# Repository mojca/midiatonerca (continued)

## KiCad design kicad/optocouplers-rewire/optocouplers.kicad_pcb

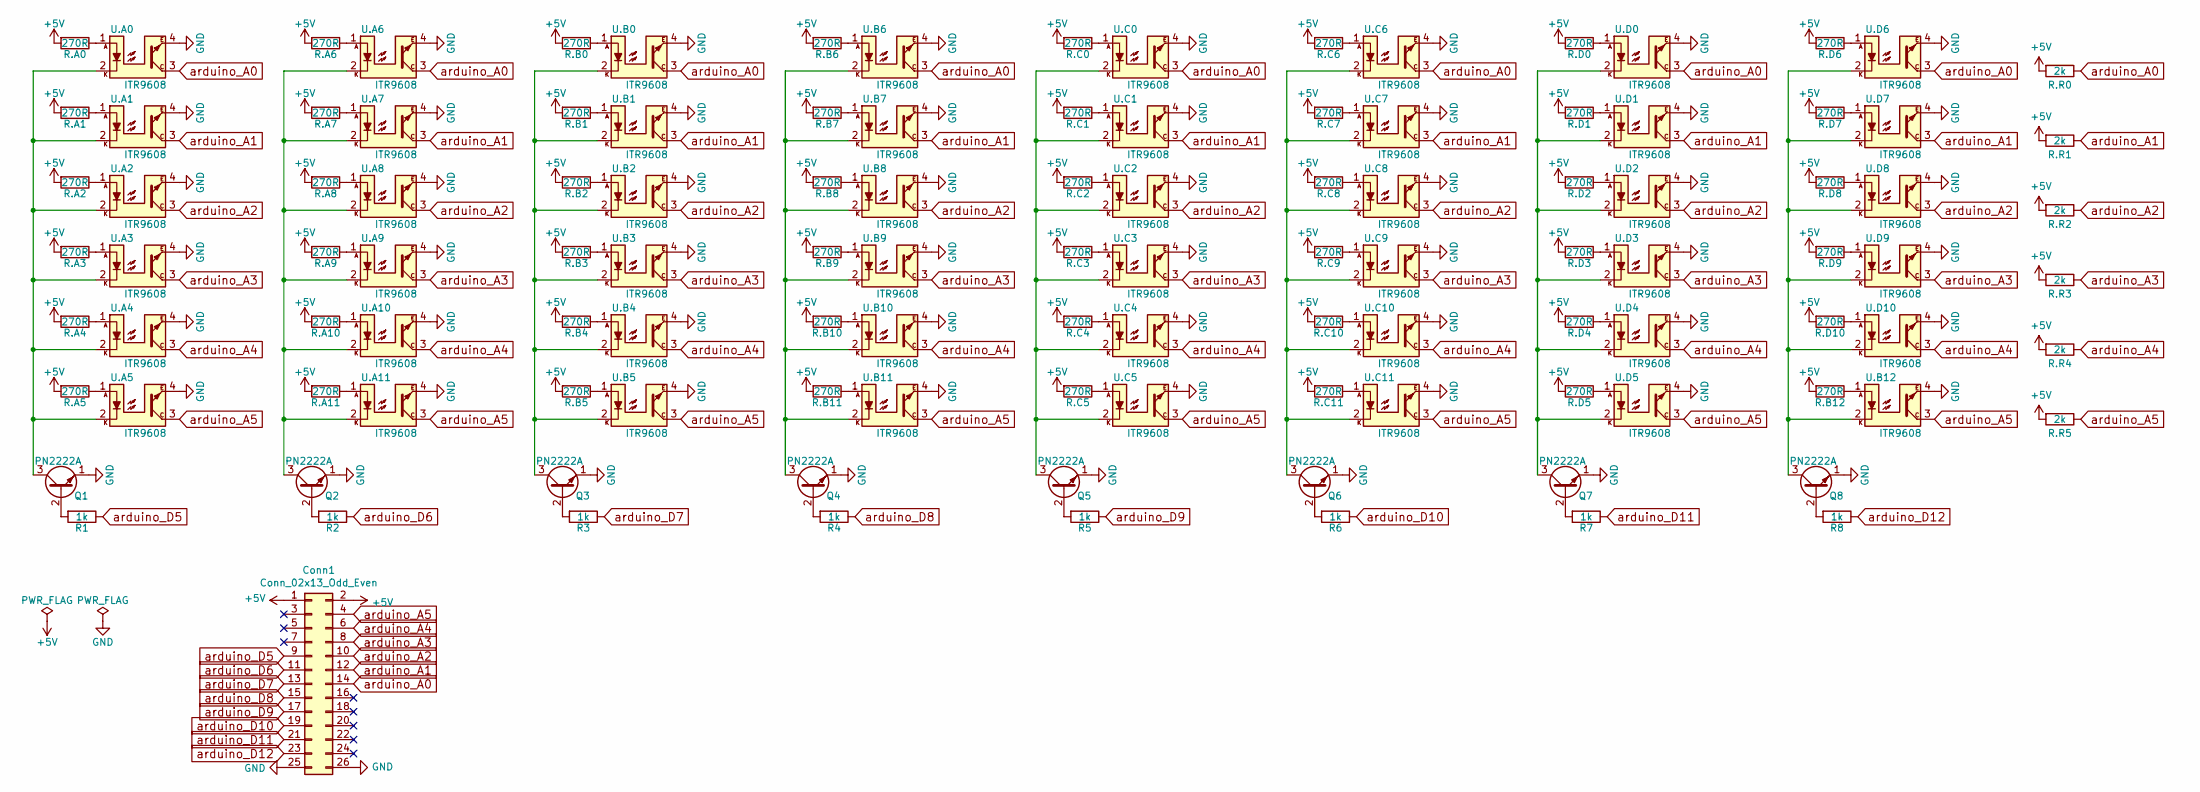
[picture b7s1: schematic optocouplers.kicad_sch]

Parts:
Conn1: Conn_02x13_Odd_Even; IDC-Header_2x13_P2.54mm_Vertical; LCSC Part # C692426
Q1, Q2, Q3, Q4, Q5, Q6, Q7, Q8: PN2222A; TO-92_Inline_Wide; LCSC Part # C184875
R1, R2, R3, R4, R5, R6, R7, R8: 1k; R_1206_3216Metric_Pad1.30x1.75mm_HandSolder; LCSC Part # C4410
R.A0, R.A1, R.A2, R.A3, R.A4, R.A5, R.A6, R.A7, R.A8, R.A9, R.A10, R.A11, R.B0, R.B1, R.B2, R.B3, R.B4, R.B5, R.B6, R.B7, R.B8, R.B9, R.B10, R.B11, R.B12, R.C0, R.C1, R.C2, R.C3, R.C4, R.C5, R.C6, R.C7, R.C8, R.C9, R.C10, R.C11, R.D0, R.D1, R.D2, R.D3, R.D4, R.D5, R.D6, R.D7, R.D8, R.D9, R.D10: 270R; R_1206_3216Metric_Pad1.30x1.75mm_HandSolder; LCSC Part # C229488
R.R0, R.R1, R.R2, R.R3, R.R4, R.R5: 2k; R_1206_3216Metric_Pad1.30x1.75mm_HandSolder; LCSC Part # C17944
U.A0, U.A1, U.A2, U.A3, U.A4, U.A5, U.A6, U.A7, U.A8, U.A9, U.A10, U.A11, U.B0, U.B1, U.B2, U.B3, U.B4, U.B5, U.B6, U.B7, U.B8, U.B9, U.B10, U.B11, U.B12, U.C0, U.C1, U.C2, U.C3, U.C4, U.C5, U.C6, U.C7, U.C8, U.C9, U.C10, U.C11, U.D0, U.D1, U.D2, U.D3, U.D4, U.D5, U.D6, U.D7, U.D8, U.D9, U.D10: ITR9608; LCSC Part # C52833

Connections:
+5V: Conn1.1, Conn1.2, R.A0.2, R.A1.2, R.A2.2, R.A3.2, R.A4.2, R.A5.2, R.A6.2, R.A7.2, R.A8.2, R.A9.2, R.A10.2, R.A11.2, R.B0.2, R.B1.2, R.B2.2, R.B3.2, R.B4.2, R.B5.2, R.B6.2, R.B7.2, R.B8.2, R.B9.2, R.B10.2, R.B11.2, R.B12.2, R.C0.2, R.C1.2, R.C2.2, R.C3.2, R.C4.2, R.C5.2, R.C6.2, R.C7.2, R.C8.2, R.C9.2, R.C10.2, R.C11.2, R.D0.2, R.D1.2, R.D2.2, R.D3.2, R.D4.2, R.D5.2, R.D6.2, R.D7.2, R.D8.2, R.D9.2, R.D10.2, R.R0.2, R.R1.2, R.R2.2, R.R3.2, R.R4.2, R.R5.2
GND: Conn1.25, Conn1.26, Q1.1 (E), Q2.1 (E), Q3.1 (E), Q4.1 (E), Q5.1 (E), Q6.1 (E), Q7.1 (E), Q8.1 (E), U.A0.4, U.A1.4, U.A2.4, U.A3.4, U.A4.4, U.A5.4, U.A6.4, U.A7.4, U.A8.4, U.A9.4, U.A10.4, U.A11.4, U.B0.4, U.B1.4, U.B2.4, U.B3.4, U.B4.4, U.B5.4, U.B6.4, U.B7.4, U.B8.4, U.B9.4, U.B10.4, U.B11.4, U.B12.4, U.C0.4, U.C1.4, U.C2.4, U.C3.4, U.C4.4, U.C5.4, U.C6.4, U.C7.4, U.C8.4, U.C9.4, U.C10.4, U.C11.4, U.D0.4, U.D1.4, U.D2.4, U.D3.4, U.D4.4, U.D5.4, U.D6.4, U.D7.4, U.D8.4, U.D9.4, U.D10.4
unnamed: Q1.2 (B), R1.2
unnamed: Q1.3 (C), U.A0.2, U.A1.2, U.A2.2, U.A3.2, U.A4.2, U.A5.2
unnamed: Q2.2 (B), R2.2
unnamed: Q2.3 (C), U.A6.2, U.A7.2, U.A8.2, U.A9.2, U.A10.2, U.A11.2
unnamed: Q3.2 (B), R3.2
unnamed: Q3.3 (C), U.B0.2, U.B1.2, U.B2.2, U.B3.2, U.B4.2, U.B5.2
unnamed: Q4.2 (B), R4.2
unnamed: Q4.3 (C), U.B6.2, U.B7.2, U.B8.2, U.B9.2, U.B10.2, U.B11.2
unnamed: Q5.2 (B), R5.2
unnamed: Q5.3 (C), U.C0.2, U.C1.2, U.C2.2, U.C3.2, U.C4.2, U.C5.2
unnamed: Q6.2 (B), R6.2
unnamed: Q6.3 (C), U.C6.2, U.C7.2, U.C8.2, U.C9.2, U.C10.2, U.C11.2
unnamed: Q7.2 (B), R7.2
unnamed: Q7.3 (C), U.D0.2, U.D1.2, U.D2.2, U.D3.2, U.D4.2, U.D5.2
unnamed: Q8.2 (B), R8.2
unnamed: Q8.3 (C), U.B12.2, U.D6.2, U.D7.2, U.D8.2, U.D9.2, U.D10.2
unnamed: R.A0.1, U.A0.1
unnamed: R.A1.1, U.A1.1
unnamed: R.A2.1, U.A2.1
unnamed: R.A3.1, U.A3.1
unnamed: R.A4.1, U.A4.1
unnamed: R.A5.1, U.A5.1
unnamed: R.A6.1, U.A6.1
unnamed: R.A7.1, U.A7.1
unnamed: R.A8.1, U.A8.1
unnamed: R.A9.1, U.A9.1
unnamed: R.A10.1, U.A10.1
unnamed: R.A11.1, U.A11.1
unnamed: R.B0.1, U.B0.1
unnamed: R.B1.1, U.B1.1
unnamed: R.B2.1, U.B2.1
unnamed: R.B3.1, U.B3.1
unnamed: R.B4.1, U.B4.1
unnamed: R.B5.1, U.B5.1
unnamed: R.B6.1, U.B6.1
unnamed: R.B7.1, U.B7.1
unnamed: R.B8.1, U.B8.1
unnamed: R.B9.1, U.B9.1
unnamed: R.B10.1, U.B10.1
unnamed: R.B11.1, U.B11.1
unnamed: R.B12.1, U.B12.1
unnamed: R.C0.1, U.C0.1
unnamed: R.C1.1, U.C1.1
unnamed: R.C2.1, U.C2.1
unnamed: R.C3.1, U.C3.1
unnamed: R.C4.1, U.C4.1
unnamed: R.C5.1, U.C5.1
unnamed: R.C6.1, U.C6.1
unnamed: R.C7.1, U.C7.1
unnamed: R.C8.1, U.C8.1
unnamed: R.C9.1, U.C9.1
unnamed: R.C10.1, U.C10.1
unnamed: R.C11.1, U.C11.1
unnamed: R.D0.1, U.D0.1
unnamed: R.D1.1, U.D1.1
unnamed: R.D2.1, U.D2.1
unnamed: R.D3.1, U.D3.1
unnamed: R.D4.1, U.D4.1
unnamed: R.D5.1, U.D5.1
unnamed: R.D6.1, U.D6.1
unnamed: R.D7.1, U.D7.1
unnamed: R.D8.1, U.D8.1
unnamed: R.D9.1, U.D9.1
unnamed: R.D10.1, U.D10.1
arduino_A0: Conn1.14, R.R0.1, U.A0.3, U.A6.3, U.B0.3, U.B6.3, U.C0.3, U.C6.3, U.D0.3, U.D6.3
arduino_A1: Conn1.12, R.R1.1, U.A1.3, U.A7.3, U.B1.3, U.B7.3, U.C1.3, U.C7.3, U.D1.3, U.D7.3
arduino_A2: Conn1.10, R.R2.1, U.A2.3, U.A8.3, U.B2.3, U.B8.3, U.C2.3, U.C8.3, U.D2.3, U.D8.3
arduino_A3: Conn1.8, R.R3.1, U.A3.3, U.A9.3, U.B3.3, U.B9.3, U.C3.3, U.C9.3, U.D3.3, U.D9.3
arduino_A4: Conn1.6, R.R4.1, U.A4.3, U.A10.3, U.B4.3, U.B10.3, U.C4.3, U.C10.3, U.D4.3, U.D10.3
arduino_A5: Conn1.4, R.R5.1, U.A5.3, U.A11.3, U.B5.3, U.B11.3, U.B12.3, U.C5.3, U.C11.3, U.D5.3
arduino_D5: Conn1.9, R1.1
arduino_D6: Conn1.11, R2.1
arduino_D7: Conn1.13, R3.1
arduino_D8: Conn1.15, R4.1
arduino_D9: Conn1.17, R5.1
arduino_D10: Conn1.19, R6.1
arduino_D11: Conn1.21, R7.1
arduino_D12: Conn1.23, R8.1

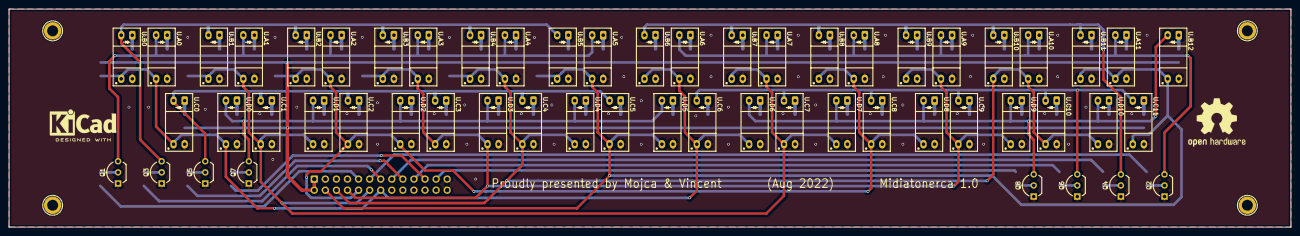
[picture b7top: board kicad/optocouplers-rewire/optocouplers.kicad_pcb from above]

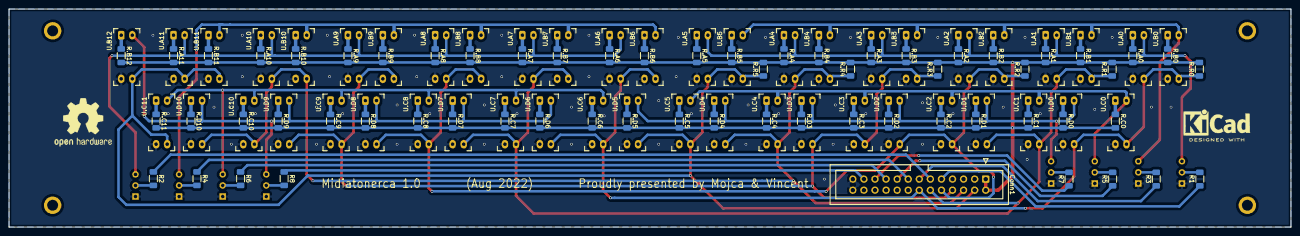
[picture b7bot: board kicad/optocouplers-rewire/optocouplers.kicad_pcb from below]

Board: 2 copper layers, 294.0 x 50.0 mm, 119 parts (63 on the bottom side), 80 nets.

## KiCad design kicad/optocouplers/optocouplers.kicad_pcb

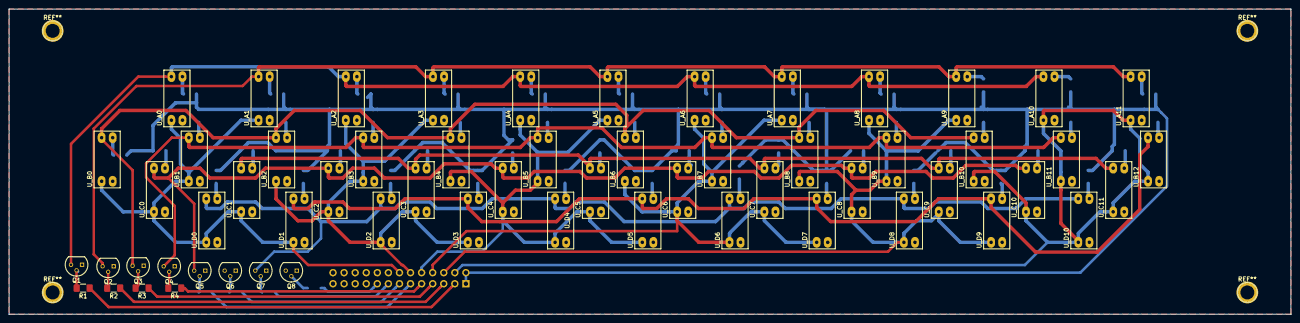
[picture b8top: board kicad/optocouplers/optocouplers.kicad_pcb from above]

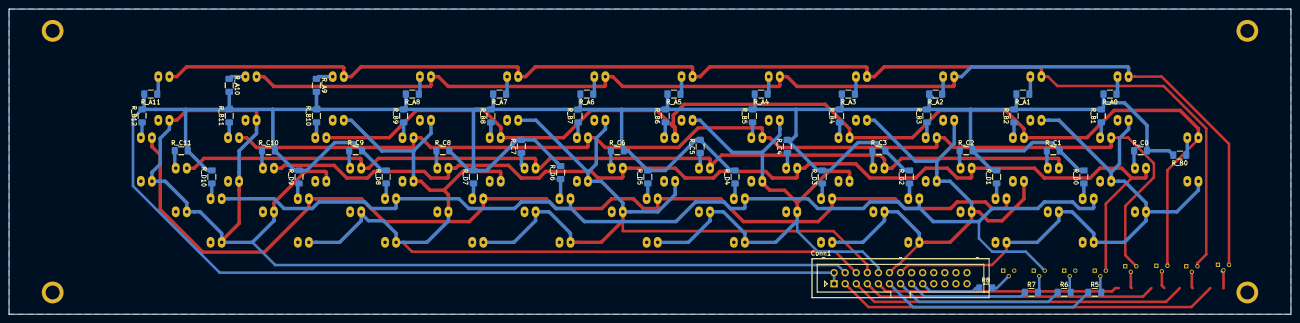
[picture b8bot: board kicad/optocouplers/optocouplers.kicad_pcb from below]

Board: 2 copper layers, 294.0 x 70.0 mm, 113 parts (53 on the bottom side), 80 nets.

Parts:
Conn1: Conn_02x13_Odd_Even; Multicomp_MC9A12-2634_2x13_P2.54mm_Vertical
Q1, Q2, Q3, Q4, Q5, Q6, Q7, Q8: PN2222A; TO-92_Molded_Narrow
R1, R2, R3, R4, R5, R6, R7, R8: 1k; R_1206_3216Metric_Pad1.42x1.75mm_HandSolder
R_A0, R_A1, R_A2, R_A3, R_A4, R_A5, R_A6, R_A7, R_A8, R_A9, R_A10, R_A11: 270R; R_1206_3216Metric_Pad1.42x1.75mm_HandSolder
R_B0, R_B1, R_B2, R_B3, R_B4, R_B5, R_B6, R_B7, R_B8, R_B9, R_B10, R_B11, R_B12: 270R; R_1206_3216Metric_Pad1.42x1.75mm_HandSolder
R_C0, R_C1, R_C2, R_C3, R_C4, R_C5, R_C6, R_C7, R_C8, R_C9, R_C10, R_C11: 270R; R_1206_3216Metric_Pad1.42x1.75mm_HandSolder
R_D0, R_D1, R_D2, R_D3, R_D4, R_D5, R_D6, R_D7, R_D8, R_D9, R_D10: 270R; R_1206_3216Metric_Pad1.42x1.75mm_HandSolder
U_A0, U_A1, U_A2, U_A3, U_A4, U_A5, U_A6, U_A7, U_A8, U_A9, U_A10, U_A11: ITR9608
U_B0, U_B1, U_B2, U_B3, U_B4, U_B5, U_B6, U_B7, U_B8, U_B9, U_B10, U_B11, U_B12: ITR9608
U_C0, U_C1, U_C2, U_C3, U_C4, U_C5, U_C6, U_C7, U_C8, U_C9, U_C10, U_C11: ITR9608
U_D0, U_D1, U_D2, U_D3, U_D4, U_D5, U_D6, U_D7, U_D8, U_D9, U_D10: ITR9608

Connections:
+5V: Conn1.1, Conn1.2, R_A0.2, R_A1.2, R_A2.2, R_A3.2, R_A4.2, R_A5.2, R_A6.2, R_A7.2, R_A8.2, R_A9.2, R_A10.2, R_A11.2, R_B0.2, R_B1.2, R_B2.2, R_B3.2, R_B4.2, R_B5.2, R_B6.2, R_B7.2, R_B8.2, R_B9.2, R_B10.2, R_B11.2, R_B12.2, R_C0.2, R_C1.2, R_C2.2, R_C3.2, R_C4.2, R_C5.2, R_C6.2, R_C7.2, R_C8.2, R_C9.2, R_C10.2, R_C11.2, R_D0.2, R_D1.2, R_D2.2, R_D3.2, R_D4.2, R_D5.2, R_D6.2, R_D7.2, R_D8.2, R_D9.2, R_D10.2
GND: Conn1.25, Conn1.26, Q1.1, Q2.1, Q3.1, Q4.1, Q5.1, Q6.1, Q7.1, Q8.1, U_A0.4, U_A1.4, U_A2.4, U_A3.4, U_A4.4, U_A5.4, U_A6.4, U_A7.4, U_A8.4, U_A9.4, U_A10.4, U_A11.4, U_B0.4, U_B1.4, U_B2.4, U_B3.4, U_B4.4, U_B5.4, U_B6.4, U_B7.4, U_B8.4, U_B9.4, U_B10.4, U_B11.4, U_B12.4, U_C0.4, U_C1.4, U_C2.4, U_C3.4, U_C4.4, U_C5.4, U_C6.4, U_C7.4, U_C8.4, U_C9.4, U_C10.4, U_C11.4, U_D0.4, U_D1.4, U_D2.4, U_D3.4, U_D4.4, U_D5.4, U_D6.4, U_D7.4, U_D8.4, U_D9.4, U_D10.4
unnamed: Q1.2, R1.2
unnamed: Q1.3, U_A0.2, U_A2.2, U_A4.2, U_A6.2, U_A8.2, U_A10.2
unnamed: Q2.2, R2.2
unnamed: Q2.3, U_A1.2, U_A3.2, U_A5.2, U_A7.2, U_A9.2, U_A11.2
unnamed: Q3.2, R3.2
unnamed: Q3.3, U_B0.2, U_B2.2, U_B4.2, U_B6.2, U_B8.2, U_B10.2
unnamed: Q4.2, R4.2
unnamed: Q4.3, U_B1.2, U_B3.2, U_B5.2, U_B7.2, U_B9.2, U_B11.2
unnamed: Q5.2, R5.2
unnamed: Q5.3, U_C0.2, U_C2.2, U_C4.2, U_C6.2, U_C8.2, U_C10.2
unnamed: Q6.2, R6.2
unnamed: Q6.3, U_C1.2, U_C3.2, U_C5.2, U_C7.2, U_C9.2, U_C11.2
unnamed: Q7.2, R7.2
unnamed: Q7.3, U_D0.2, U_D2.2, U_D4.2, U_D6.2, U_D8.2, U_D10.2
unnamed: Q8.2, R8.2
unnamed: Q8.3, U_B12.2, U_D1.2, U_D3.2, U_D5.2, U_D7.2, U_D9.2
unnamed: R_A0.1, U_A0.1
unnamed: R_A1.1, U_A1.1
unnamed: R_A2.1, U_A2.1
unnamed: R_A3.1, U_A3.1
unnamed: R_A4.1, U_A4.1
unnamed: R_A5.1, U_A5.1
unnamed: R_A6.1, U_A6.1
unnamed: R_A7.1, U_A7.1
unnamed: R_A8.1, U_A8.1
unnamed: R_A9.1, U_A9.1
unnamed: R_A10.1, U_A10.1
unnamed: R_A11.1, U_A11.1
unnamed: R_B0.1, U_B0.1
unnamed: R_B1.1, U_B1.1
unnamed: R_B2.1, U_B2.1
unnamed: R_B3.1, U_B3.1
unnamed: R_B4.1, U_B4.1
unnamed: R_B5.1, U_B5.1
unnamed: R_B6.1, U_B6.1
unnamed: R_B7.1, U_B7.1
unnamed: R_B8.1, U_B8.1
unnamed: R_B9.1, U_B9.1
unnamed: R_B10.1, U_B10.1
unnamed: R_B11.1, U_B11.1
unnamed: R_B12.1, U_B12.1
unnamed: R_C0.1, U_C0.1
unnamed: R_C1.1, U_C1.1
unnamed: R_C2.1, U_C2.1
unnamed: R_C3.1, U_C3.1
unnamed: R_C4.1, U_C4.1
unnamed: R_C5.1, U_C5.1
unnamed: R_C6.1, U_C6.1
unnamed: R_C7.1, U_C7.1
unnamed: R_C8.1, U_C8.1
unnamed: R_C9.1, U_C9.1
unnamed: R_C10.1, U_C10.1
unnamed: R_C11.1, U_C11.1
unnamed: R_D0.1, U_D0.1
unnamed: R_D1.1, U_D1.1
unnamed: R_D2.1, U_D2.1
unnamed: R_D3.1, U_D3.1
unnamed: R_D4.1, U_D4.1
unnamed: R_D5.1, U_D5.1
unnamed: R_D6.1, U_D6.1
unnamed: R_D7.1, U_D7.1
unnamed: R_D8.1, U_D8.1
unnamed: R_D9.1, U_D9.1
unnamed: R_D10.1, U_D10.1
arduino_A0: Conn1.14, U_A0.3, U_A1.3, U_B0.3, U_B1.3, U_C0.3, U_C1.3, U_D0.3, U_D1.3
arduino_A1: Conn1.12, U_A2.3, U_A3.3, U_B2.3, U_B3.3, U_C2.3, U_C3.3, U_D2.3, U_D3.3
arduino_A2: Conn1.10, U_A4.3, U_A5.3, U_B4.3, U_B5.3, U_C4.3, U_C5.3, U_D4.3, U_D5.3
arduino_A3: Conn1.8, U_A6.3, U_A7.3, U_B6.3, U_B7.3, U_C6.3, U_C7.3, U_D6.3, U_D7.3
arduino_A4: Conn1.6, U_A8.3, U_A9.3, U_B8.3, U_B9.3, U_C8.3, U_C9.3, U_D8.3, U_D9.3
arduino_A5: Conn1.4, U_A10.3, U_A11.3, U_B10.3, U_B11.3, U_B12.3, U_C10.3, U_C11.3, U_D10.3
arduino_D5: Conn1.3, R1.1
arduino_D6: Conn1.5, R2.1
arduino_D7: Conn1.7, R3.1
arduino_D8: Conn1.9, R4.1
arduino_D9: Conn1.11, R5.1
arduino_D10: Conn1.13, R6.1
arduino_D11: Conn1.15, R7.1
arduino_D12: Conn1.17, R8.1

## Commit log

2017-07-24 revision 3 and 4 of 3D design
2017-07-24 alternative keyboard plates
2017-07-24 dxf files for keyboards
2017-07-26 Version 5 of mechanical design
2017-07-26 test dxf conversion from pstoedit
2017-07-26 test eps
2017-07-26 test dxf
2017-07-26 add dxf files for revision 5
2017-07-26 add zips
2017-07-26 revision 6
2017-07-27 alt keyboard
2017-07-28 optocoupler board
2017-07-31 testing design for the keyboard
2017-07-31 Added schematic for octocoupler backplate
2017-07-31 start creating a pattern
2017-07-31 keyboard pcb: two lines
2017-07-31 full board for keyboard
2017-08-01 nearly final version of keyboard PCB
2017-08-02 Arduino code for LeverHarmonica added
2017-08-03 Single button MIDI latency tester
2017-08-04 Added support for different patches. Serial baudrate now defaults to 31250.
2017-08-04 Add two semitones for the fourth row
2017-08-04 version of printed pcb
2017-08-05 Add handling for the second harmonika
2017-08-05 Fix debounce on second accordion
2019-09-15 Added Arduino project: BassButtonTester. Actually also for testing treble buttons. Different pin assignments can be configured. Analog sensor readings can be inspected, as well as single row/column d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
    BassButton is a class which makes it easy to embed it in different projects and hide the complexity of the implementation.
2022-06-21 Updates bass side etc in Enschede
2022-07-28 SpecialInstrument implemented
2022-07-28 Remove trailing spaces
2022-07-28 Specify buttons with names
2022-07-28 Add an optional test routine which is run if a flag is set
    The test routine continuously produces one simple note.
    Baudrate changed to 115200, to avoid the 31250/38400 bug in SamplerBox.
    Some more corrections and changes and updates.
2022-07-29 Defined bass and chords for 2-row harmonica
2022-07-29 Clean-up bass names
2022-07-29 Fix bass heights
2022-07-29 Added support to count the number of buttons playing the same note.
    Multiple buttons may play the same note. noteON is sent for each one, but noteOFF only for the last one.
2022-07-29 Support for multiple keypresses for the same note.
2022-07-29 Changing patch or instrument now stops notes. Note numbers 0 no longer transferred. Code cleaned up.
    When changing patch or instrument type (2-row or 4-row) the currently playing notes are now stopped, to avoid noteOFF mismatch.
    If note number is 0 then it is no longer sent as noteON or noteOFF to the SamplerBox.
    Code has been cleaned up.
2022-08-01 Add some basic LED lighting and push/pull button
2022-08-01 set serial speed
2022-08-02 Patch updated with new studio recording, and non-midi text messages update
    Patch 0 now contains the studio recording from Aug 1, 2022. The recording in Mojca's room has been moved to patch 15.
    The MIDI message function now only outputs messages if midi note is nonzero, both in midi and non-midi mode.
2022-09-14 New pin and bank mapping, separate include files for midi notes and instrument patches, autodetect switch inversion.
    In the Aug/Sept 2022 update new PCBs were developed for lever and cherry key accordions. The key mapping has changed: instead of 6 banks we now have 8 banks.
    A new project was created: "LeverHarmonica_EightBanks_Sept2022" so that the old project (LeverHarmonica) is still compatible with our 1st iteration (wooden harmonica). In the new project separate hea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
2022-11-23 Added EightBanks version of arduino code
2023-12-28 Implemented Native MIDI in LeverHarmonica_EightBanks script
    Native MIDI is now supported. Nano 33 IoT must be used as Arduino controller from now on. The older Nano 3.0 does not support native MIDI.
    The script is still backwards compatible with Patchbox-style MIDI-over-Serial-over-USB by setting NATIVE_MIDI = false.
2024-01-01 Moved unused versions to subdirectories
2024-01-01 Implemented LEDs
    LEDs willl light up according to:
    depressed, decayTimeMs > decayMax: 10%
    depressed, decayTimeMs < decayMax: map(decayTimeMs, 0, 50, decayMax, 25)
    pressed: 100% (set decayTimeMs = 0)
    released: initially 50%, decays to 25% during one second
2024-01-02 Set MIDI note offsets to 0 for all patches
2024-01-28 Expanded some debugging code to help solving some issues
    Fix stuff
2024-03-04 schematic for optocouplers
2024-03-04 cherry-mx basses
2024-03-04 update kicad drawings for optocouplers
2024-03-04 Add labels to optocoupler board
2024-03-04 Slightly change wiring of optocouplers
2024-03-04 add arduino to cherry keys
2024-03-04 Update to the latest version of optocoupler pcb design
2024-03-04 fix reference names on PCB
2024-03-04 Copy of optocouplers (temporary)
2024-03-04 Add schematic for new optocouplers board
2024-03-04 Assign correct footprint of transistors, missing resistors
2024-03-04 intermediate step of optocoupler pcb
2024-03-04 [PCB] cherry basses: changes in lib
    Not exactly sure what these changes are ...
2024-03-04 Add schematic for cherry treble
2024-03-04 Pick compatible PCB components for cherry trebble
2024-03-04 temp commit with pcb
2024-03-04 Add two mounting holes and refill background of cherry basses
2024-03-04 Add missing 2k resistors, change connectors (opto)
2024-03-04 Backup of optocouplers
2024-03-04 Save cherry basses with kicad 6
2024-03-04 remove all segments from optocouplers board
2024-03-04 Use correct components (.net) for optocouple board
2024-03-04 almost complete pcb
2024-03-04 Almost finished pcb
2024-03-04 This change removed background fill from optocouplers board
    It was probably done by accident and might need reverting
2024-03-04 Fix silkscreen text on cherry basses
2024-03-04 cache lib for optocouplers PCB
2024-03-04 Add edge cut to cherry basses
2024-03-04 unfinished changes in optocouplers board
2024-03-04 Finish cherry basses keyboard
2024-03-04 rename some components in schematic
2024-03-04 Update components
2024-03-04 No clue what this changed (TODO)
2024-03-04 move a single optocoupler
2024-03-04 No clue what changed
2024-03-04 swap a1 and a6
2024-03-04 slightly align two resistors, update pcb from schematic, prepare before fixing names of components
2024-03-04 Remove the background drawing of optocouplers
2024-03-04 Move around optocouplers for rows A and C
2024-03-04 Rename elements on pcb
2024-03-04 remove segments
2024-03-04 Temporary move some resistors around
2024-03-04 Remove the drawing of a single optocoupler
2024-03-04 align optocouplers for line C
2024-03-04 Can the net list be deleted?
2024-03-04 Fix placements of components for the row A
2024-03-04 Fix placement of row b
2024-03-04 change uuids of resistors
2024-03-04 fix placement of components for row D
2024-03-04 rename uuids
2024-03-04 old sch file is no longer needed (optocouplers)
2024-03-04 fix placements of resistors for row c
2024-03-04 move resistors to the back of the list as they belong to the back cu
2024-03-04 Remove paths
2024-03-04 some nearly straight lines
2024-03-04 Place resistors R.R0 to R.R5
2024-03-04 Move optocouplers 1 mm higher (TODO: one resistor belongs to a different commit)
2024-03-04 Move some resistors a bit
2024-03-04 fix resistor location
2024-03-04 straight lines
2024-03-04 fix typo in resistor uuid
2024-03-04 Simple connections between neighbours
2024-03-04 Unfinished PCB for cherry treble
2024-03-04 Exclude cherry switches from BOM
2024-03-04 5V line
2024-03-04 Update wiring schematic for cherry treble
2024-03-04 Some project settings for cherry basses
2024-03-04 Add some lines
2024-03-04 More lines
2024-03-04 Add Neltron connectors
2024-03-04 Update pcb for cherry basses
    - add connector for the side button
    - fix vias
    - fix positions of some diodes
2024-03-04 Update cherry treble PCB
2024-03-04 cherry basses pcb: no clue what changed
2024-03-04 Move connector closer to the keys on cherry treble
    Almost enforce the clearance
2024-03-04 Project and settings for cherry basses
2024-03-04 optocouplers project
2024-03-04 Replace the cherry basses schematic with the new one
2024-03-04 Move optocouplers to the correct place, shrink the board
2024-03-04 optocouplers schematic
2024-03-04 optocouplers prl
2024-03-04 Move pushpull switch name on cherry basses
2024-03-04 Potentially finished cherry treble pcb
2024-03-04 cherry basses: replace components for rendering, add some vias
2024-03-04 Shrink kicad treble, fix interline spacing
2024-03-04 Move elements of the cherry treble PCB
2024-03-04 shrink cherry treble pcb by 2 mm on each side
2024-03-04 Further dimension adjustments to cherry treble to fit into the box
2024-03-04 Define clearance to 0.5 mm for cherry treble
2024-03-04 Refill zones
2024-03-04 Exclude connector on cherry treble from BOM
2024-03-04 Define origin
2024-03-04 optocouplers: change footprints
2024-03-04 Name the diodes on cherry treble
2024-03-04 Exclude connector from position file
2024-03-04 Remove cherry switches from assembly files
2024-03-04 Add part numbers for resistors in cherry treble schematics
2024-03-04 Add LCSC part # for resistors
2024-03-04 Add exclude_from_bom to cherry treble
2024-03-04 Exclude mounting holes from assembly
2024-03-04 Rename diodes on the PCB (probably not needed, might be reverted)
2024-03-04 No clue what this changes in cherry treble prl
2024-03-04 Update optocouplers project
2024-03-04 Refill optocouplers pcb
2024-03-04 gerber settings for optocouplers
2024-03-04 Move the whole optocouplers board a bit up, finish tracing
2024-03-04 Add LCSC part numbers for the optocoupler schematics
2024-03-04 optocouplers, continue wiring
2024-03-04 Add part numbers to optocouplers
2024-03-04 Autoplace fields on cherry treble schematics
2024-03-04 Add kicad & osh symbols to cherry treble pcb
2024-03-04 Use the new footprint for ITR9608
2024-03-04 Replace rescued elements with proper / newer ones
2024-03-04 Blue cherry treble board
2024-03-04 Add text to the optocouplers pcb
2024-03-04 Add arduino port labels
2024-03-04 Update footprints for optocouplers in the PCB
2024-03-04 Avoid 90 degree corners in cherry treble pcb
2024-03-04 Update diodes from schematic and fix polarity on cherry treble pcb
2024-03-04 Update part numbers for the schottky diodes plus whatever refill took place
2024-03-04 Make pcb blue
2024-03-04 Replace diode symbols on cherry treble
2024-03-04 Add OSH and KiCad logos on the silkscreen
2024-03-04 Fix part number for the schottky diodes
2024-03-04 Move led-strip schematic a bit
2024-03-04 Replace pspice diodes with proper schottky diodes on cherry basses schematics
2024-03-04 First arduino plate PCB
2024-03-04 LED strip schematic & pcb
2024-03-04 Add labels to the connector
2024-03-04 Replace mounting holes and update components from library (cherry basses)
2024-03-04 led strip project update
2024-03-04 led strip levers: unfinished PCB
2024-03-04 Add footprint for a mini toggle SPDT switch B068BW
2024-03-04 Add osh logo
2024-03-04 Updates to arduino
2024-03-04 cherry basses: update color, fix diode orientation, remove border from silk screen
2024-03-04 First version of RPi audio hat
2024-03-04 Some rounding changes to the cherry basses pcb
2024-03-04 led strip pcb: improve pad connections at the end, positive polarity zone ipd.
2024-03-04 Unplace axis origin
2024-03-04 Schematic for the LED strip for levers
2024-03-05 rpi-audio-hat: upgrade schematic to KiCad and remove side rows for rpi
2024-03-05 Update PCB for RPi audio hat
2024-03-05 3D model for screw terminal
2024-03-05 Provisional 3D model for PCM5102A
2024-03-05 3D model for the switch
2024-03-05 Update switch to KiCad8, add a link to 3D model
2024-03-05 Add footprint for PCM5102 module
2024-03-05 Add footprint for PAM8302
2024-03-05 Update RPi hat pcb
2024-03-06 Work on schematic
2024-03-06 Save PCB
2024-03-06 Fix power switch & symbol update
2024-03-07 Fix TLV761
